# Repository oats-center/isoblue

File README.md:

# Avena: Edge computing for the farm.

## What is Avena?

**Avena** is the accumulation of the lessoned learned while developing the [OATS
Center][oats-center] [ISOBlue][isoblue] project. Avena is a software foundation
suitable for devices like ISOBlue, but with more flexible data collection,
streaming, deployment, configuration, etc then ISOBlue originally had.

The operating system is based on Debian and includes modern tools, such as:
Docker, Wireguard, GPS/Chrony timesync, SSH CA, etc. The core is delivered and
maintained by [Ansible][ansible], know as the `oats.avena` collection on Ansible
Galaxy. In many cases, as long as you have a device that supports Debian (or
similar), Avena should be installable.

#### Origin of "Avena"

The word "avena" means oats in Spanish. "Oats" stands for our center's name:
**O**pen **A**g **T**echnology and **S**ystems Center.

#### What is in this repo

This repo contains all development files for Avena and ISOblue related projects,
including but not limited to:

- Avena Ansible scripts
- Hardware expansions design for supported platforms
- Case/enclosure designs for supported platforms
- Software for ISOBlue
- Documentation's

## Where is ISOBlue?

Don't worry, ISOBlue is still here to stay! The newer versions of ISOBlue are
powered by Avena, leveraging docker for most of functionality. With this setup,
ISOBlue is still the CAN bus to cloud logger we all know and love, but with
additional multi-user edge computing capabilities.

## What is ISOBlue (for those that don't know)?

[ISOBlue](https://www.isoblue.org/) is an open-source project. Its main goal is
to create a set of open-source agricultural telematic device that collects and
streams [ISO 11783](https://en.wikipedia.org/wiki/ISO_11783) (ISOBUS) data from
modern agricultural machines. The most recent iteration, ISOBlue 2.0, runs Linux
on a single board computer that is equipped with a cell modem, a SSD, and a USB
GPS module for network connectivity, storage, and positioning purposes.

# Using Avena to manage your fleet

The latest release of the Avena collections can be downloaded using the
`ansible-galaxy` command. But first, you must create an Ansible project for your
fleet and define the inventory. This guide will walk you through our recommend
setup.

Much of this is based on Jeff Geerling's excellent "[Ansible best practices:
using project-local collections and roles][geerling-best-practice]" article. We
think you should read it.

**TODO:** _Make an open-source version of `oats-fleet` as an example._

## Create a project folder

We recommend that you create a folder of ansible configurations, galaxy
collections, roles, and playbooks for your fleet. Ansible has several folder
structures that they support, our favorite is something like:

```
.
├── ansible.cfg
├── ansible_collections
│   └── oats
│       └── avena
├── inventory
│   ├── group_vars
│   │   └── fleet.yml
│   ├── hosts
│   └── host_vars
│       ├── device-1.yml
│       ├── device-2.yml
│       └── device-3.yml
├── isoblue.yml
├── isoblue-hd.yml
├── roles
│   └── custom-tests
│       ├── files
│       ├── templates
│       ├── defaults
│       └── custom-tests.yml
└── requirements.yml
```

Where:

- `isoblue.yml` and `isoblue-hd.yml` are examples of playbooks that depend
  on Avena collection roles, but also contain custom tasks for each specific
  device type in your fleet.
- `device-1.yml`, `device-2.yml`, and `device-3.yml`
  are example host variable files for the hostnames (defined in `hosts`)
  `device-1`, `device-2`, and `device-3`, respectfully.
- `fleet.yml` are group variables for the hosts within the `fleet` group as
  defined in the `hosts` file.

This folder may also contain any standard Ansible file, e.g., `roles` and used
within playbooks like any Ansible project.

For more details, check out Ansible's [content organization
documentation][ansible-content-org].

## Create an ansible.cfg

We recommend Jeff Geerling's minimal default ([source][geerling-best-practice]).

This configuration forces galaxy installed collections and roles to live within
the project, rather then your home directory. This improves repeatable
builds/runs. We also strongly recommend that you consider committing
`ansible_collections` to version control (as Jeff also suggests), at least until
`ansible-galaxy` has a true version locking scheme.

```ini
[defaults]

nocows = True
collections_paths = ./
roles_path = ./roles
```

## Creating a requirements.yml

`requirements.yml` defines what Ansible Galaxy dependencies are needed for the
project. For a basic Avena deployment, only the `oats.avena` collection is
needed. If you don't know what version you need, then you should probably use
whatever is newest.

```yml
---
collections:
  - name: oats.avena
    version: 0.1.0
```

## Installing ansible requirements

#### From Galaxy (typical)

```console
$ ansible-galaxy install -r requirements.yml
```

#### From a build

```console
$ ansible-galaxy collection install oats-avena-0.1.0.tar.gz
```

#### From git

**Note:** _This method ignores requirements.yml for the Avena collection. Be
sure to properly release your changes and update requirements.yml when your
done._

I find it easiest to clone this repo locally and link it into your projects
`ansible_collections` folder. Something like

```console
$ ln -rs ../isoblue-avena/ansible/avena ./ansible_collections/oats/`
```

when at the root of your project and `isoblue-avena` is cloned into the path
`../isoblue-avena` relative your project.

## Create a fleet playbook

If you don't already have one, create a playbook for your fleet. Here you can
add any type of custom tasks and roles as you would like. To deploy Avena, you
must include at least the `oats.avena.core` role.

For example, the below playbook would deploy the Avena core along with GPS time
synchronization, enable a cell modem, use CA based SSH authentication, and a
wireguard VPN.

```yml
- hosts: fleet
  roles:
    - oats.avena.core
    - oats.avena.gps_time
    - oats.avena.cell
    - oats.avena.ca
    - oats.avena.wireguard
```

## Vault (if using `avena-ca`)

#### Connecting to Vault

_Note: There are other ways to connect / authenticate with vault. This is an
example of `userpass`._

```console
$ export VAULT_ADDR="http://172.16.0.1:8200"
$ vault login -method=userpass username=avena
Password (will be hidden): <enter-password>
```

#### Obtaining a certificate

A certificate is only need after the initial deploy. A plain password is used to
authenticate until the `avena-ca` role completes. However, if the deploy
fails, you may also need one to restart the process.

```console
$ vault write -field=signed_key avena-client-signer/sign/admin public_key=@$HOME/.ssh/id_ed25519.pub > ~/.ssh/id_ed25519-cert.pub
```

Where a Vault CA signer is mounted at `avena-client-signer` with sufficient
permissions for the `admin` role and an ed25519 SSH user key.

# Deploying a new node

1. Install Debian using your hardware platform's [installation
   guide](../hardware/).
2. Add the node to your fleet's inventory and configure variables as needed.
3. Update your systems Vault CA certificate (if needed) using the Vault section
   above.
4. Complete the initial deploy by running the following from within your project
   folder:

   ```console
   ANSIBLE_HOST_KEY_CHECKING=False ansible-playbook isoblue.yml -i inventory --limit device-1 -e "ansible_ssh_host=10.0.0.2" -k
   ```

   Where,

   - `ANSIBLE_HOST_KEY_CHECKING=False`: _Optional_. Disable host key checking because it is
     unlikely that you have already manually approved the installation's default
     host key. The default key will be replaced by an ed25519 key. You will need
     to locally trust that key before any future Ansible commands.

     - Note: If using `avena-ca`, then all you need to trust on your local
       computer is the CA key. After that, all fleet nodes are trusted.

   - `-e - "ansible_ssh_host=<host-ip>"`: _Optional_. Temporarily overrides the
     host address. Ansible variables will still be set by the hostfile
     defination, but Ansible will SSH into the provided IP address. This is
     useful:

     - The node deployed is being deployed on a local network, but the final
       public IP is already known.
     - The node will use a Wireguard (or similar) VPN and the hostfile
       reflects the VPN address.

   - `-k`: _Optional_. Enter the SSH password at runtime. This is useful when
     using `avena-ca` (or some other password less based authentication). The
     initial deploy is authenticated by password, but all following Ansible
     commands are password less.
     - If passwords will always be used, then you could securely store each
       node's password in the inventory with Ansible vault (not to be
       confused with Hashicorp Vault from above).

# Updating nodes

1. Update your systems Vault CA certificate (if needed) using the Vault section above.
2. Run the playbook of intrest

```console
   $ ansible-playbook isoblue.yml -i inventory/
```

_Note: You can include the `--limit` flag if you want to work on some nodes_

[ansible]: https://docs.ansible.com/
[oats-center]: https://oatscenter.org
[isoblue]: https://www.isoblue.org
[geerling-best-practice]: https://www.jeffgeerling.com/blog/2020/ansible-best-practices-using-project-local-collections-and-roles
[ansible-content-org]: https://docs.ansible.com/ansible/latest/user_guide/playbooks_best_practices.html#content-organization

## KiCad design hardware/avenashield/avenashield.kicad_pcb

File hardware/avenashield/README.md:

# ISOBlue-AvenaShield

KiCad hardware schematic and PCB layout design files for the AvenaShield expansion board.

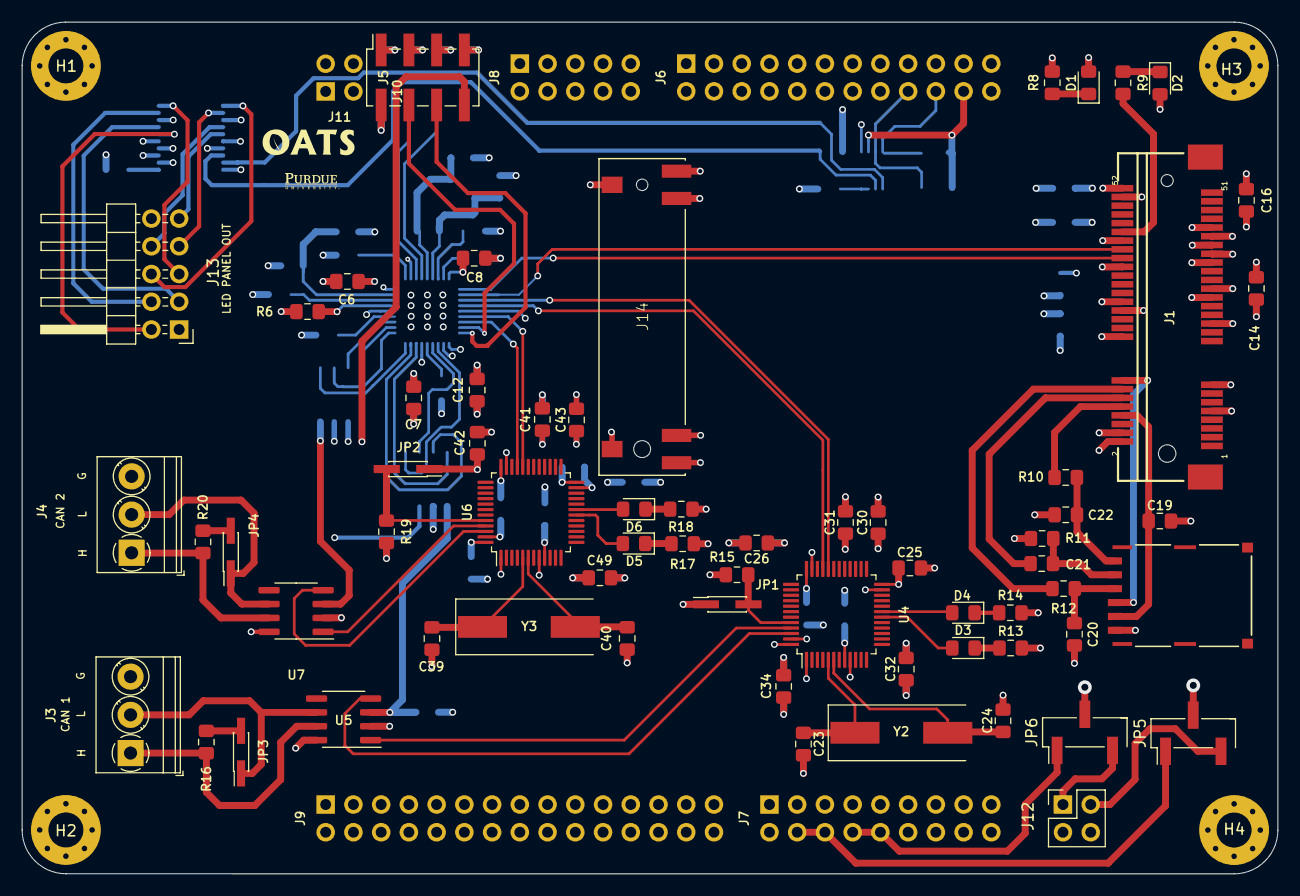
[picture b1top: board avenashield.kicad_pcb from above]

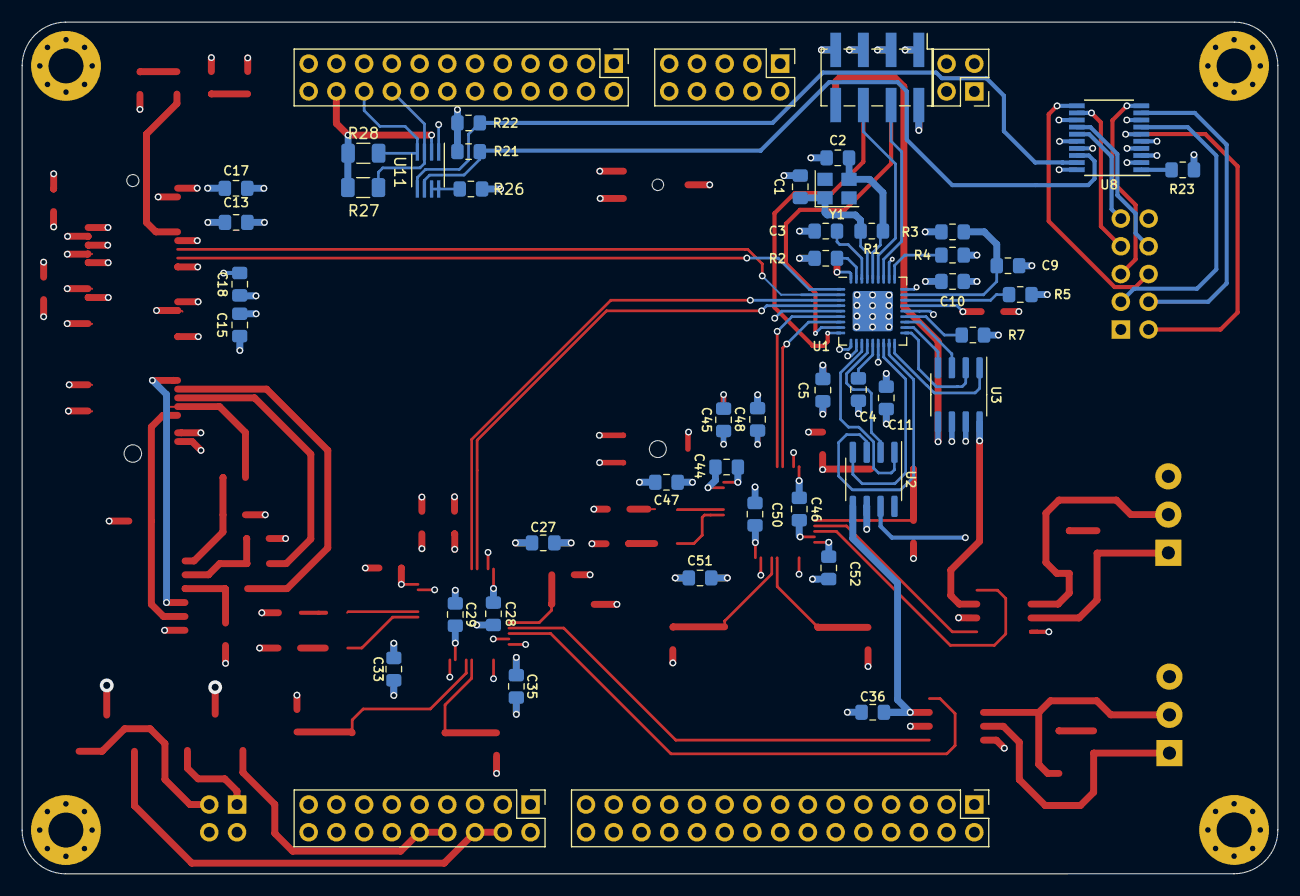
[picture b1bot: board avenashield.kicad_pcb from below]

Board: 4 copper layers, 115.0 x 78.0 mm, 118 parts (50 on the bottom side), 88 nets.

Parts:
C1, C2: 18pF; C_0805_2012Metric_Pad1.15x1.40mm_HandSolder
C3, C4, C5, C6, C7, C8, C9, C10, C11: 0.1uF; C_0805_2012Metric_Pad1.15x1.40mm_HandSolder
C12: 4.7uF; C_0805_2012Metric_Pad1.15x1.40mm_HandSolder
C13, C14, C16, C17: 100u; C_0805_2012Metric_Pad1.15x1.40mm_HandSolder
C15, C18, C19: 100n; C_0805_2012Metric_Pad1.15x1.40mm_HandSolder
C20, C21, C22: 33p; C_0805_2012Metric_Pad1.15x1.40mm_HandSolder
C23, C24, C39, C40: 18p; C_0805_2012Metric_Pad1.15x1.40mm_HandSolder
C25, C26, C27, C29, C30, C34, C36, C41, C42, C43, C45, C46, C50, C52: 0.1u; C_0805_2012Metric_Pad1.15x1.40mm_HandSolder
C28, C31, C35, C44, C47, C51: 4.7u; C_0805_2012Metric_Pad1.15x1.40mm_HandSolder
C32, C48: 10n; C_0805_2012Metric_Pad1.15x1.40mm_HandSolder
C33, C49: 1u; C_0805_2012Metric_Pad1.15x1.40mm_HandSolder
D1: MODEM_PWR; LED_0805_2012Metric_Pad1.15x1.40mm_HandSolder
D2: WWAN; LED_0805_2012Metric_Pad1.15x1.40mm_HandSolder
D3, D4, D5, D6: LED; LED_0805_2012Metric_Pad1.15x1.40mm_HandSolder
H1: MOUNT_PAD1; MountingHole_3.2mm_M3_Pad_Via
H2: MOUNT_PAD2; MountingHole_3.2mm_M3_Pad_Via
H3: MOUNT_PAD3; MountingHole_3.2mm_M3_Pad_Via
H4: MOUNT_PAD4; MountingHole_3.2mm_M3_Pad_Via
J1: Bus_PCI_Express_Mini; TE_1775862-2
J2: SIM_Card; CONN-693043020611
J3: CAN_TRA_HEADER; TerminalBlock_Phoenix_PT-1,5-3-3.5-H_1x03_P3.50mm_Horizontal
J4: CAN_IMP_HEADER; TerminalBlock_Phoenix_PT-1,5-3-3.5-H_1x03_P3.50mm_Horizontal
J5: USB Headers Board Top; PinSocket_2x04_P2.54mm_Vertical_SMD
J6: Lattepanda Upper Left Header (I2C and I2S); PinHeader_2x12_P2.54mm_Vertical
J7: Lattepanda Upper Right Header (BIOS SPI); PinHeader_2x09_P2.54mm_Vertical
J8: Lattepanda Middle Left Header (RS-232); PinHeader_2x05_P2.54mm_Vertical
J9: Lattepanda Lower Right Header (Arduino Pins); PinHeader_2x15_P2.54mm_Vertical
J10: Lattepanda Lower Left Header (USB); PinHeader_2x04_P2.54mm_Vertical_SMD
J11: 12V DC IN Headers; PinHeader_2x02_P2.54mm_Vertical
J12: EXT PWR IN; PinHeader_2x02_P2.54mm_Vertical
J13: LED_OUT; PinHeader_2x05_P2.54mm_Horizontal
J14: JAE_MM60-EZH059-B5-R650
JP1, JP2: Boot Mode; PinHeader_2x01_P1.27mm_Vertical_SMD
JP3: Termination Enable; PinHeader_2x01_P1.27mm_Vertical_SMD
JP4: Termination enable; PinHeader_2x01_P1.27mm_Vertical_SMD
JP5: 3.3V SRC SEL; PinHeader_1x03_P2.54mm_Vertical_SMD_Pin1Left
JP6: 5V SRC SEL; PinHeader_1x03_P2.54mm_Vertical_SMD_Pin1Left
R1: 1M; R_0805_2012Metric_Pad1.15x1.40mm_HandSolder
R2: 12k; R_0805_2012Metric_Pad1.15x1.40mm_HandSolder
R3, R4, R5, R6, R7: 100k; R_0805_2012Metric_Pad1.15x1.40mm_HandSolder
R8, R9: 330; R_0805_2012Metric_Pad1.15x1.40mm_HandSolder
R10, R11, R12: 47; R_0805_2012Metric_Pad1.15x1.40mm_HandSolder
R13, R14, R16, R17, R18, R20: 120; R_0805_2012Metric_Pad1.15x1.40mm_HandSolder
R15, R19: 510; R_0805_2012Metric_Pad1.15x1.40mm_HandSolder
R21, R22, R23: 4.7k; R_0805_2012Metric_Pad1.15x1.40mm_HandSolder
R26: 200k; R_0805_2012Metric_Pad1.15x1.40mm_HandSolder
R27, R28: 4.7k; R_1206_3216Metric
U1: USB2514B_Bi; QFN-36-1EP_6x6mm_P0.5mm_EP3.7x3.7mm
U2, U3: MIC2026-1BM; SOIC-8_3.9x4.9mm_P1.27mm
U4, U6: STM32F042C6Tx; LQFP-48_7x7mm_P0.5mm
U5, U7: MCP2551-I-SN; SOIC-8_3.9x4.9mm_P1.27mm
U8: TLC59108xPW; TSSOP-20_4.4x6.5mm_P0.65mm
U11: PCA9306; SSOP-8_2.95x2.8mm_P0.65mm
Y1: 24 MHz; Crystal_SMD_3225-4Pin_3.2x2.5mm
Y2, Y3: 16 MHz; Crystal_SMD_HC49-SD

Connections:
+3V3: C5.1, C6.1, C7.1, C8.1, C10.1, C11.1, C12.1, C13.1, C14.1, C15.1, C16.1, C17.1, C18.1, C25.1, C26.1, C27.1, C28.1, C29.1, C30.1, C31.1, C32.1, C33.1, C34.1, C35.1, C41.1, C42.1, C43.1, C44.1, C45.1, C46.1, C47.1, C48.1, C49.1, C50.1, C51.1, C52.1, D1.2, J1.2, J1.24, J1.39, J1.41, J1.52, JP1.1, JP2.1, JP5.1, R3.1, U1.5, U1.10, U1.15, U1.23, U1.27, U1.29, U1.36, U4.1, U4.9, U4.24, U4.36, U4.48, U6.1, U6.9, U6.24, U6.36, U6.48
+5V: J13.1, JP6.1, R21.1, R22.1, R26.1, U2.7, U3.7, U8.17, U8.20
/Lattepanda/EXT_3V3: J12.2, JP5.2
/Lattepanda/EXT_5V: J12.1, JP6.2
/Lattepanda/PANDA_1V8: J6.22, R27.1, R28.1, U11.2
/Lattepanda/PANDA_3V3: J7.4, J7.6, JP5.3
/Lattepanda/PANDA_5V: J7.8, J7.10, JP6.3
/Lattepanda/PANDA_SCL: J6.18, R27.2, U11.3
/Lattepanda/PANDA_SDA: J6.20, R28.2, U11.4
/Lattepanda/USB_DM: J10.4, U1.30
/Lattepanda/USB_DP: J10.6, U1.31
/MiniPCIe2USB.sch/USB_DM: J1.36, U1.1
/MiniPCIe2USB.sch/USB_DP: J1.38, U1.2
/USB2CAN_IMP/CAN_H: J4.1, R20.1, U7.7
/USB2CAN_IMP/CAN_L: J4.2, JP4.1, U7.6
/USB2CAN_IMP/CAN_RX: U6.45, U7.1
/USB2CAN_IMP/CAN_TX: U6.46, U7.4
/USB2CAN_IMP/USB_DM: U1.6, U6.32
/USB2CAN_IMP/USB_DP: U1.7, U6.33
/USB2CAN_TRA/CAN_H: J3.1, R16.1, U5.7
/USB2CAN_TRA/CAN_L: J3.2, JP3.1, U5.6
/USB2CAN_TRA/CAN_RX: U4.45, U5.1
/USB2CAN_TRA/CAN_TX: U4.46, U5.4
/USB2CAN_TRA/USB_DM: U1.3, U4.32
/USB2CAN_TRA/USB_DP: U1.4, U4.33
/USB_HEADERS/USB_DM: J5.4, U1.8
/USB_HEADERS/USB_DP: J5.6, U1.9
/USB_HUB/PRT_PWR_2: C36.2, U2.5, U5.3
/USB_HUB/PRT_PWR_3: U3.8, U7.3
/USB_HUB/PRT_PWR_4: J5.8, U3.5
GNDREF: C1.2, C2.2, C3.2, C4.2, C5.2, C6.2, C7.2, C8.2, C9.2, C10.2, C11.2, C12.2, C13.2, C14.2, C15.2, C16.2, C17.2, C18.2, C19.2, C20.2, C21.2, C22.2, C23.2, C24.2, C25.2, C26.2, C27.2, C28.2, C29.2, C30.2, C31.2, C32.2, C33.2, C34.2, C35.2, C36.1, C39.2, C40.2, C41.2, C42.2, C43.2, C44.2, C45.2, C46.2, C47.2, C48.2, C49.2, C50.2, C51.2, C52.2, D2.2, H1.1, H2.1, H3.1, H4.1, J1.4, J1.9, J1.15, J1.18, J1.21, J1.26, J1.27, J1.29, J1.34, J1.35, J1.37, J1.40, J1.43, J1.50, J2.5, J3.3, J4.3, J5.1, J5.2, J5.3, J5.5, J5.7, J6.1, J6.17, J6.19, J6.21, J6.23, J10.1, J10.2, J10.3, J10.5, J10.7, J12.3, J12.4, J13.10, J14.S1_1, J14.S1_2, J14.S1_3, J14.S2_1, J14.S2_2, J14.S2_3, R2.2, R4.2, R5.2, R6.2, R7.2, R8.2, R13.2, R14.2, R15.2, R17.2, R18.2, R19.2, R23.2, U1.11, U1.37, U2.6, U3.6, U4.8, U4.23, U4.35, U4.47, U5.2, U5.8, U6.8, U6.23, U6.35, U6.47, U7.2, U7.8, U8.2, U8.3, U8.4, U8.5, U8.8, U8.13, U8.16, U11.1
unnamed: C1.1, R1.1, U1.33, Y1.1
unnamed: C2.1, R1.2, U1.32, Y1.2
unnamed: C3.1, U1.34
unnamed: C4.1, U1.14
unnamed: C9.1, R3.2, U1.26
unnamed: C19.1, J1.8, J2.1
unnamed: C20.1, J2.2, R12.1
unnamed: C21.1, J2.3, R11.1
unnamed: C22.1, J2.7, R10.1
unnamed: C23.1, U4.5, Y2.1
unnamed: C24.1, U4.6, Y2.2
unnamed: C39.1, U6.5, Y3.1
unnamed: C40.1, U6.6, Y3.2
unnamed: D1.1, R8.1
unnamed: D2.1, R9.1
unnamed: D3.1, R13.1
unnamed: D3.2, U4.18
unnamed: D4.1, R14.1
unnamed: D4.2, U4.19
unnamed: D5.1, R17.1
unnamed: D5.2, U6.18
unnamed: D6.1, R18.1
unnamed: D6.2, U6.19
unnamed: J1.10, R10.2
unnamed: J1.12, R11.2
unnamed: J1.14, R12.2
unnamed: J1.16, J2.6
unnamed: J1.42, R9.2
unnamed: J13.2, U8.6
unnamed: J13.3, U8.7
unnamed: J13.4, U8.9
unnamed: J13.5, U8.10
unnamed: J13.6, U8.11
unnamed: J13.7, U8.12
unnamed: J13.8, U8.14
unnamed: J13.9, U8.15
unnamed: JP1.2, R15.1, U4.44
unnamed: JP2.2, R19.1, U6.44
unnamed: JP3.2, R16.2
unnamed: JP4.2, R20.2
unnamed: R2.1, U1.35
unnamed: R4.1, U1.28
unnamed: R5.1, U1.25
unnamed: R6.1, U1.24
unnamed: R7.1, U1.22
unnamed: R21.2, U8.18, U11.6
unnamed: R22.2, U8.19, U11.5
unnamed: R23.1, U8.1
unnamed: R26.2, U11.7, U11.8
unnamed: U1.12, U2.1
unnamed: U1.13, U2.2
unnamed: U1.16, U2.4
unnamed: U1.17, U2.3
unnamed: U1.18, U3.1
unnamed: U1.19, U3.2
unnamed: U1.20, U3.4
unnamed: U1.21, U3.3

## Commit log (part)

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2020-08-26 Addition of sanity check if number of containers mismatches the number specified in docker-compose
2020-08-27 Add can-watchdog container to list of containers to test
2020-09-01 Implementation of can device searching and dbus suspend. Still not in a working state due to issues with bind mounts not following symbolic links
2020-09-02 Switched to underscore instead of dash
2020-09-03 Containerization of can-watchdog (#63)
    * First pass of can-watchdog without dbus suspend
    * Removal of old can-watchdog
    * Add can-watchdog container to list of containers to test
    * Bugfixes and verification testing on dev board 5
    * Implementation of can device searching and dbus suspend. Still not in a working state due to issues with bind mounts not following symbolic links
    * Changing bind mount point
2020-09-18 Add oats2 ga runner
2020-09-22 Add docker-compose pull commands
2020-09-25 Container-maintainer transition to --remove-orphans flag (#78)
2020-09-29 oada_upload db index and renaming sent triggers (#80)
    * Addition of index and sent triggers
    * Centralize function/trigger removal
2020-10-01 Added multistage build to socketcand container
2020-10-01 Rework workflow for releases
2020-10-02 Fixed syntax error in can_logger.py
2020-10-02 Added CAN interface selection env. variables
2020-10-02 Initial database health check
2020-10-07 Undoing testing changes to docker-compose file
2020-10-14 Enabling can labels in ansible
2020-11-02 Successfully read and insert data from file
2020-11-03 Fixed high speed bus issues
2020-11-18 gps.py wait for it
    Refactoring zmq and nng stuff, added support to gps.py to wait for dbus and
    postgre startup, switch to python3 slim docker packages for all containers
    dealing with gps and gps testing
2020-11-30 Revert "Syntax fix"
    This reverts commit c982a8b97d4005fa51a3f671fe4df58d387b2a25.
2020-12-27 Splitting up github actions yml files
    Moved integration tests to own file to allow them to be run parallel
    and renamed files as appropiate
2021-01-21 Fixed mispelled variable
2021-01-22 Removed unwanted readme file from hardware directory
2021-01-26 x86 preseed file
    Currently a seperate file, would like to merge with the toradex version
2021-02-02 Whitespace fix
2021-02-03 Docs
2021-02-03 Moving testing containers, move dbus to volume
2021-02-18 Further ansible bugfixes
    Forcing grub config to not insert spaces to avoid syntax errors in config file, add installtion of dependencies due to new changes in docker-compose build
2021-02-23 Add: lorawand skeleton code
2021-03-05 Initial gps-exporter code
2021-03-05 Missed the critical part ...
2021-03-09 First pass, semi working
2021-03-10 Added log rotation settings through docker-compose
2021-03-15 Add rust target folder to gitignore
2021-03-17 Actually remove the debug printing
2021-03-21 Update control_messages.rs
    Cast tv_sec for armv7
2021-04-12 Checkpoint commit
2021-04-22 new database, added inserts
2021-05-04 Try linux/arm/v5 instead
2021-05-12 Bump docker/setup-qemu-action from 1 to 1.1.0
    Bumps [docker/setup-qemu-action](https://github.com/docker/setup-qemu-action) from 1 to 1.1.0.
    - [Release notes](https://github.com/docker/setup-qemu-action/releases)
    - [Commits](https://github.com/docker/setup-qemu-action/compare/v1...v1.1.0)
2021-05-12 Temp removal of multistage build
2021-05-30 Bump ws from 7.3.0 to 7.4.6 in /services/oada_upload
    Bumps [ws](https://github.com/websockets/ws) from 7.3.0 to 7.4.6.
    - [Release notes](https://github.com/websockets/ws/releases)
    - [Commits](https://github.com/websockets/ws/compare/7.3.0...7.4.6)
2021-07-13 try new platform fix
2021-08-23 Bump docker/build-push-action from 2.6.1 to 2.7.0
    Bumps [docker/build-push-action](https://github.com/docker/build-push-action) from 2.6.1 to 2.7.0.
    - [Release notes](https://github.com/docker/build-push-action/releases)
    - [Commits](https://github.com/docker/build-push-action/compare/v2.6.1...v2.7.0)
    ---
    updated-dependencies:
    - dependency-name: docker/build-push-action
2021-10-18 Bump actions/checkout from 2.3.4 to 2.3.5
    Bumps [actions/checkout](https://github.com/actions/checkout) from 2.3.4 to 2.3.5.
    - [Release notes](https://github.com/actions/checkout/releases)
    - [Changelog](https://github.com/actions/checkout/blob/main/CHANGELOG.md)
    - [Commits](https://github.com/actions/checkout/compare/v2.3.4...v2.3.5)
    ---
    updated-dependencies:
2021-11-03 Bump actions/checkout from 2.3.4 to 2.4.0
    Bumps [actions/checkout](https://github.com/actions/checkout) from 2.3.4 to 2.4.0.
    - [Release notes](https://github.com/actions/checkout/releases)
    - [Changelog](https://github.com/actions/checkout/blob/main/CHANGELOG.md)
    - [Commits](https://github.com/actions/checkout/compare/v2.3.4...v2.4.0)
    ---
    updated-dependencies:
2021-11-23 Bump actions/cache from 2.1.6 to 2.1.7
    Bumps [actions/cache](https://github.com/actions/cache) from 2.1.6 to 2.1.7.
    - [Release notes](https://github.com/actions/cache/releases)
    - [Commits](https://github.com/actions/cache/compare/v2.1.6...v2.1.7)
    ---
    updated-dependencies:
    - dependency-name: actions/cache
2022-01-19 Bump docker/build-push-action from 2.6.1 to 2.8.0
    Bumps [docker/build-push-action](https://github.com/docker/build-push-action) from 2.6.1 to 2.8.0.
    - [Release notes](https://github.com/docker/build-push-action/releases)
    - [Commits](https://github.com/docker/build-push-action/compare/v2.6.1...v2.8.0)
    ---
    updated-dependencies:
    - dependency-name: docker/build-push-action
2022-02-23 Bump mszostok/codeowners-validator from 0.6.0 to 0.7.1
    Bumps [mszostok/codeowners-validator](https://github.com/mszostok/codeowners-validator) from 0.6.0 to 0.7.1.
    - [Release notes](https://github.com/mszostok/codeowners-validator/releases)
    - [Changelog](https://github.com/mszostok/codeowners-validator/blob/main/.goreleaser.yml)
    - [Commits](https://github.com/mszostok/codeowners-validator/compare/v0.6.0...v0.7.1)
    ---
    updated-dependencies:
2022-03-15 Bump docker/build-push-action from 2.9.0 to 2.10.0
    Bumps [docker/build-push-action](https://github.com/docker/build-push-action) from 2.9.0 to 2.10.0.
    - [Release notes](https://github.com/docker/build-push-action/releases)
    - [Commits](https://github.com/docker/build-push-action/compare/v2.9.0...v2.10.0)
    ---
    updated-dependencies:
    - dependency-name: docker/build-push-action
2022-04-11 Bump actions/checkout from 2.4.0 to 3.0.0
    Bumps [actions/checkout](https://github.com/actions/checkout) from 2.4.0 to 3.0.0.
    - [Release notes](https://github.com/actions/checkout/releases)
    - [Changelog](https://github.com/actions/checkout/blob/main/CHANGELOG.md)
    - [Commits](https://github.com/actions/checkout/compare/v2.4.0...v3.0.0)
    ---
    updated-dependencies:
2022-04-14 Kept gps_nats. changed ip to localhost
2022-04-15 forgot to submit build and push thing i think
2022-04-29 Bump docker/setup-buildx-action from 1.6.0 to 1.7.0
    Bumps [docker/setup-buildx-action](https://github.com/docker/setup-buildx-action) from 1.6.0 to 1.7.0.
    - [Release notes](https://github.com/docker/setup-buildx-action/releases)
    - [Commits](https://github.com/docker/setup-buildx-action/compare/v1.6.0...v1.7.0)
    ---
    updated-dependencies:
    - dependency-name: docker/setup-buildx-action
2022-06-06 Bump zeroize_derive from 1.0.1 to 1.3.2 in /services/j1939d
    Bumps [zeroize_derive](https://github.com/RustCrypto/utils) from 1.0.1 to 1.3.2.
    - [Release notes](https://github.com/RustCrypto/utils/releases)
    - [Changelog](https://github.com/RustCrypto/utils/blob/master/zeroize/CHANGELOG.md)
    - [Commits](https://github.com/RustCrypto/utils/compare/base64ct-v1.0.1...zeroize_derive-v1.3.2)
    ---
    updated-dependencies:
2022-06-06 Bump regex from 1.4.5 to 1.5.6 in /services/j1939d
    Bumps [regex](https://github.com/rust-lang/regex) from 1.4.5 to 1.5.6.
    - [Release notes](https://github.com/rust-lang/regex/releases)
    - [Changelog](https://github.com/rust-lang/regex/blob/master/CHANGELOG.md)
    - [Commits](https://github.com/rust-lang/regex/compare/1.4.5...1.5.6)
    ---
    updated-dependencies:
2022-06-12 Removed loop parameter from run function
2022-06-13 Added AVENA_PREFIX to subject string
2022-08-08 Bump docker/build-push-action from 2.10.0 to 3.1.1
    Bumps [docker/build-push-action](https://github.com/docker/build-push-action) from 2.10.0 to 3.1.1.
    - [Release notes](https://github.com/docker/build-push-action/releases)
    - [Commits](https://github.com/docker/build-push-action/compare/v2.10.0...v3.1.1)
    ---
    updated-dependencies:
    - dependency-name: docker/build-push-action
2022-09-26 changed prometheus prefix to j1939
2022-09-26 fixed typo in dockerfile
2022-09-27 dropped cross inside dockerfile
2022-09-27 changed to buster as base on cell_logger dockerfile
2022-10-04 Bump actions/cache from 3.0.8 to 3.0.10
    Bumps [actions/cache](https://github.com/actions/cache) from 3.0.8 to 3.0.10.
    - [Release notes](https://github.com/actions/cache/releases)
    - [Changelog](https://github.com/actions/cache/blob/main/RELEASES.md)
    - [Commits](https://github.com/actions/cache/compare/v3.0.8...v3.0.10)
    ---
    updated-dependencies:
2022-10-13 Bump docker/setup-buildx-action from 2.0.0 to 2.1.0
    Bumps [docker/setup-buildx-action](https://github.com/docker/setup-buildx-action) from 2.0.0 to 2.1.0.
    - [Release notes](https://github.com/docker/setup-buildx-action/releases)
    - [Commits](https://github.com/docker/setup-buildx-action/compare/v2.0.0...v2.1.0)
    ---
    updated-dependencies:
    - dependency-name: docker/setup-buildx-action
2022-12-13 Bump actions/checkout from 3.1.0 to 3.2.0
    Bumps [actions/checkout](https://github.com/actions/checkout) from 3.1.0 to 3.2.0.
    - [Release notes](https://github.com/actions/checkout/releases)
    - [Changelog](https://github.com/actions/checkout/blob/main/CHANGELOG.md)
    - [Commits](https://github.com/actions/checkout/compare/v3.1.0...v3.2.0)
    ---
    updated-dependencies:
2023-01-06 Bump tokio from 1.8.4 to 1.18.4 in /services/gps-exporter
    Bumps [tokio](https://github.com/tokio-rs/tokio) from 1.8.4 to 1.18.4.
    - [Release notes](https://github.com/tokio-rs/tokio/releases)
    - [Commits](https://github.com/tokio-rs/tokio/compare/tokio-1.8.4...tokio-1.18.4)
    ---
    updated-dependencies:
    - dependency-name: tokio
2023-01-20 Bump bumpalo from 3.6.1 to 3.12.0 in /services/gps-exporter
    Bumps [bumpalo](https://github.com/fitzgen/bumpalo) from 3.6.1 to 3.12.0.
    - [Release notes](https://github.com/fitzgen/bumpalo/releases)
    - [Changelog](https://github.com/fitzgen/bumpalo/blob/main/CHANGELOG.md)
    - [Commits](https://github.com/fitzgen/bumpalo/compare/3.6.1...3.12.0)
    ---
    updated-dependencies:
2023-03-10 Bump actions/cache from 3.0.10 to 3.3.0
    Bumps [actions/cache](https://github.com/actions/cache) from 3.0.10 to 3.3.0.
    - [Release notes](https://github.com/actions/cache/releases)
    - [Changelog](https://github.com/actions/cache/blob/main/RELEASES.md)
    - [Commits](https://github.com/actions/cache/compare/v3.0.10...v3.3.0)
    ---
    updated-dependencies:
2023-06-05 Bump actions/checkout from 3.3.0 to 3.5.2
    Bumps [actions/checkout](https://github.com/actions/checkout) from 3.3.0 to 3.5.2.
    - [Release notes](https://github.com/actions/checkout/releases)
    - [Changelog](https://github.com/actions/checkout/blob/main/CHANGELOG.md)
    - [Commits](https://github.com/actions/checkout/compare/v3.3.0...v3.5.2)
    ---
    updated-dependencies:
2023-06-08 Bump docker/setup-buildx-action from 2.2.1 to 2.6.0
    Bumps [docker/setup-buildx-action](https://github.com/docker/setup-buildx-action) from 2.2.1 to 2.6.0.
    - [Release notes](https://github.com/docker/setup-buildx-action/releases)
    - [Commits](https://github.com/docker/setup-buildx-action/compare/v2.2.1...v2.6.0)
    ---
    updated-dependencies:
    - dependency-name: docker/setup-buildx-action
2023-06-29 Bump docker/setup-buildx-action from 2.2.1 to 2.8.0
    Bumps [docker/setup-buildx-action](https://github.com/docker/setup-buildx-action) from 2.2.1 to 2.8.0.
    - [Release notes](https://github.com/docker/setup-buildx-action/releases)
    - [Commits](https://github.com/docker/setup-buildx-action/compare/v2.2.1...v2.8.0)
    ---
    updated-dependencies:
    - dependency-name: docker/setup-buildx-action
2023-07-20 added exception handling to JSON parser
2023-08-04 fixed requirements.txt
